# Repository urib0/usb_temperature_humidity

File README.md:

# usb_temperature_humidity
Mac, LinuxマシンにUSBで接続できて追加ドライバ不要で値を読める温湿度センサ

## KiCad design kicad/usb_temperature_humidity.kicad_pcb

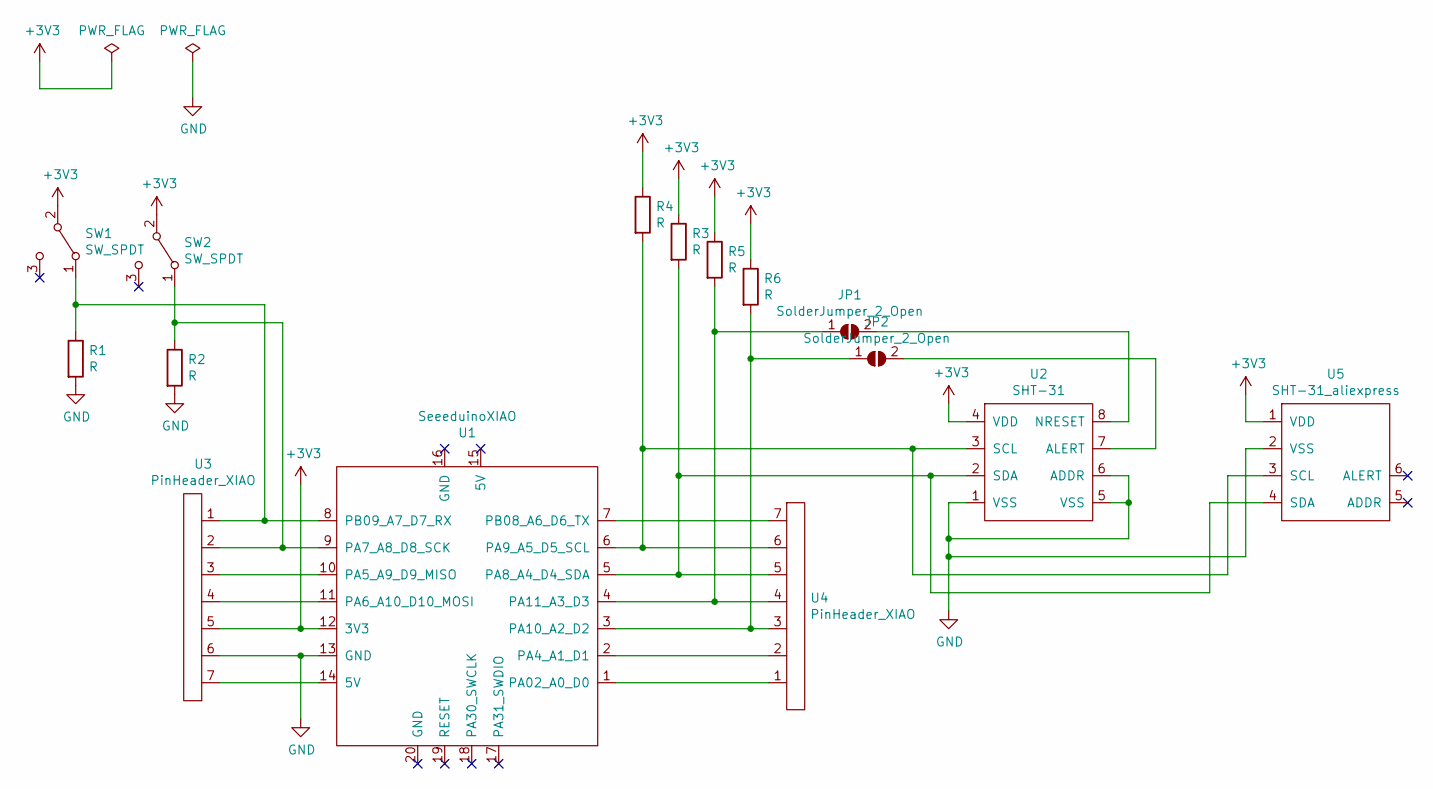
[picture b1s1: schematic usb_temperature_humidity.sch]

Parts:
JP1, JP2: SolderJumper_2_Open; SolderJumper-2_P1.3mm_Open_TrianglePad1.0x1.5mm
R1, R2, R3, R4, R5, R6: R; R_Axial_DIN0207_L6.3mm_D2.5mm_P10.16mm_Horizontal
SW1, SW2: SW_SPDT; SW_SLIDE_sengoku
U1: SeeeduinoXIAO; SeeedXIAO
U2: SHT-31
U3, U4: PinHeader_XIAO
U5: SHT-31_aliexpress

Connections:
+3V3: R3.1, R4.1, R5.1, R6.1, SW1.2 (B), SW2.2 (B), U1.12 (3V3), U2.4 (VDD), U3.5, U5.1 (VDD)
GND: R1.2, R2.2, U1.13 (GND), U2.1 (VSS), U2.5 (VSS), U2.6 (ADDR), U3.6, U5.2 (VSS)
unnamed: JP1.1 (A), R5.2, U1.4 (PA11_A3_D3), U4.4
unnamed: JP1.2 (B), U2.8 (NRESET)
unnamed: JP2.1 (A), R6.2, U1.3 (PA10_A2_D2), U4.3
unnamed: JP2.2 (B), U2.7 (ALERT)
unnamed: R1.1, SW1.1 (A), U1.8 (PB09_A7_D7_RX), U3.1
unnamed: R2.1, SW2.1 (A), U1.9 (PA7_A8_D8_SCK), U3.2
unnamed: R3.2, U1.5 (PA8_A4_D4_SDA), U2.2 (SDA), U4.5, U5.4 (SDA)
unnamed: R4.2, U1.6 (PA9_A5_D5_SCL), U2.3 (SCL), U4.6, U5.3 (SCL)
unnamed: U1.1 (PA02_A0_D0), U4.1
unnamed: U1.2 (PA4_A1_D1), U4.2
unnamed: U1.7 (PB08_A6_D6_TX), U4.7
unnamed: U1.10 (PA5_A9_D9_MISO), U3.3
unnamed: U1.11 (PA6_A10_D10_MOSI), U3.4
unnamed: U1.14 (5V), U3.7

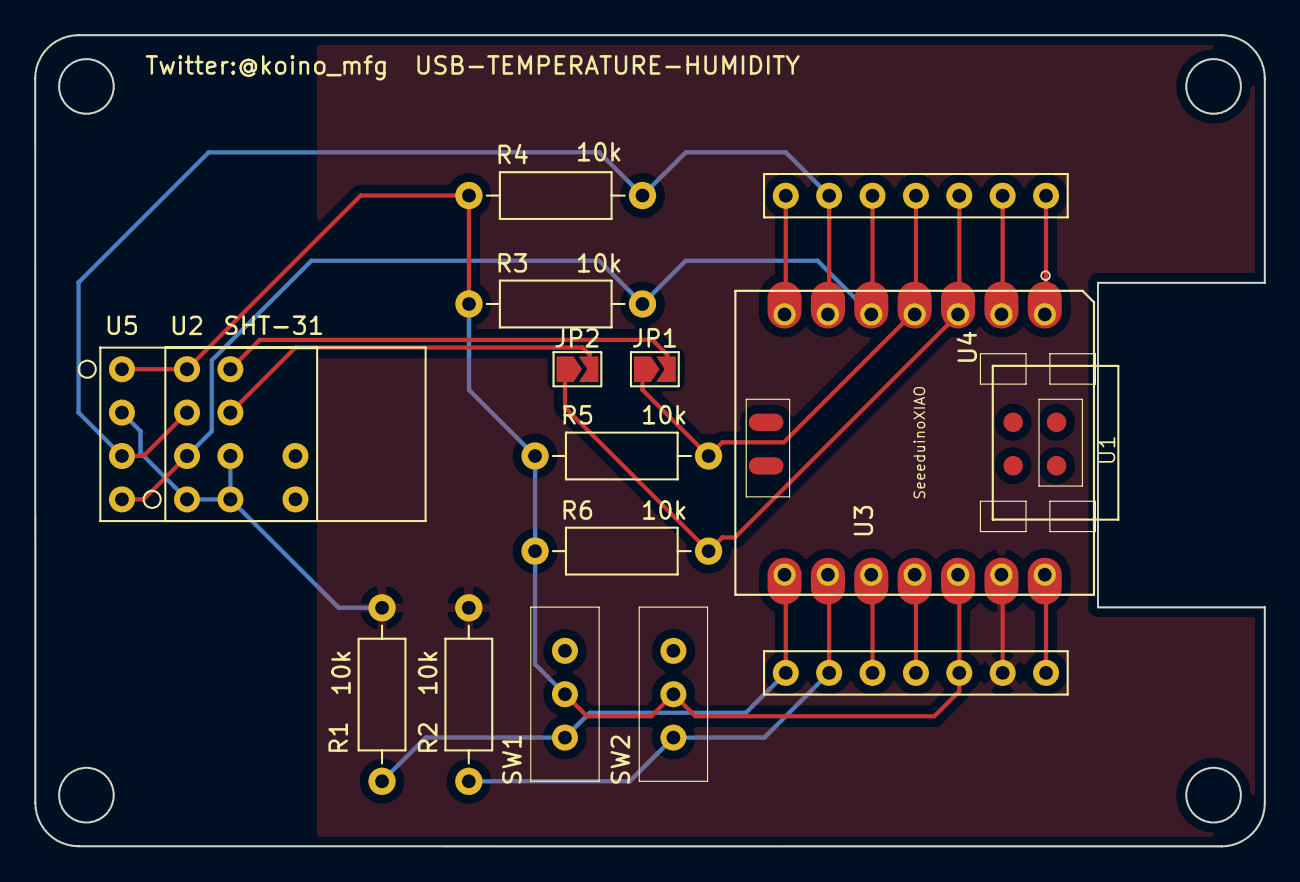
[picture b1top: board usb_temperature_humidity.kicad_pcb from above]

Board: 2 copper layers, 72.0 x 47.5 mm, 15 parts (0 on the bottom side), 16 nets.

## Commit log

2020-08-21 add gitignore
2020-08-21 回路図引いた
2020-08-24 使うか分からんけどスイッチ追加した
2020-08-24 抵抗のナンバリングが気持ち悪かったので直した
2020-08-24 ピンヘッダのナンバリングが気持ち悪かったのでXIAOのピン番号に合わせた
2020-08-24 とりあえず設計した
2020-08-24 ガーバー出力用の設定をした
2020-08-25 ガーバーデータを追加
2020-09-08 arduino スケッチのファイル名を修正
2020-09-09 初期化処理実装
2020-09-09 温度湿度のレジスタを読むところまで実装
2020-09-09 温湿度を算出して渡すようにした
2020-09-09 温湿度を読んで1秒毎にシリアル出力するようにした
2020-09-17 シリアル出力にステータスをつけた
2020-09-25 改行コードを修正した
2020-11-17 フットプリントの更新と、SHT-31のADDRピンをGNDに落とした
2020-11-17 基板外形を秋月Cタイプ基板に合わせた
2020-11-17 抵抗の容量をシルクに記載した
2020-11-17 SHT-31の1ピンにシルクでマークをつけた
2020-11-17 REALGLOBEのロゴを入れた
2020-11-17 DRC OK
2020-11-17 XIAOのピンヘッダを1x1の標準ライブラリから1x7の自作ライブラリに変えた
2020-11-18 OPENジャンパを介してALERT,NRESETをXIAOに繋いだ
2020-11-18 DRD OK
2020-12-02 aliexpress版のSHT-31をスキーマに追加した
2020-12-02 シンボルをaliexpressのSHT-31に置き換えた
2020-12-02 配線済みDRC ok
2020-12-02 バージョンシルクのインクリメントをした
2020-12-08 SHT-31モジュールに1ピンのシルクをつけた
2021-06-06 フォーマッタをかけた
2021-06-06 シリアル出力にバージョンを追加した(1.00)
2021-06-13 基板上の署名をkoinoにした
2021-06-17 バージョン定義抜けを修正
2021-07-09 画像とモデルを出力した
